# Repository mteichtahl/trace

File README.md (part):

# trace

trace runs a repository by itself and gives Claude the tools to do electronics work in it. It is generalised from
the loop that runs Potroller.

- **The loop.** A pushed branch gets its pull request, stacked on the open pull request it builds on when it builds on
  one (docs/stacked-changes.md). A PR merges itself when its required check passes, bottom of a stack first, and open
  PRs are brought up to date one at a time. A failing build is triaged: flaky failures are re-run, and real ones go to
  Claude, which fixes them. Deploys run behind a risk check, a smoke test and an automatic rollback. A person is asked
  only when a project's rules say so, or when the loop is stuck.
- **The tools.** These cover KiCad (reading schematics and boards, ERC/DRC, BOM, fabrication outputs), component
  calculators, SPICE and Verilog simulation, a datasheet library and parts database shared by every project,
  hardware-in-the-loop (serial, CAN, and SCPI power supplies, scopes and meters), and the firmware loop (build, flash,
  logs). They are reachable from the `tracectl` CLI and, for Claude Code, from the `trace` MCP server.

## Installing

```sh
npm install -g github:mteichtahl/trace#main    # the `tracectl` CLI (Node 22.13+; git, which this needs anyway)
tracectl install                               # opens the installer in your browser
```

The command is `tracectl`, not `trace`: macOS ships its own `/usr/bin/trace` (kernel tracing), and a `trace` on
`PATH` would shadow it, or be shadowed by it wherever nvm's directory is not first (sudo, cron, launchd). The
product, the MCP server (`claude mcp add trace -- tracectl mcp`) and `.trace/` keep the name.

**What you need:** AWS credentials (a profile, SSO included, or access keys; an administrator is simplest) and one
GitHub token. Nothing else: no Docker, no `gh` CLI, no KiCad or Python on this machine (the images build in
CodeBuild, and onboarding talks to GitHub's API and `git`).

The token: a fine-grained token (github.com/settings/personal-access-tokens) on the repositories trace will run, with
Contents, Pull requests, Issues, Workflows, Actions, Secrets, Variables, Administration and Webhooks read and write,
Deployments read, and the account permission "Email addresses: read"; or a classic token with `repo`, `workflow` and `user:email`. What each
permission is for, and what happens without it, is in [Tokens and permissions](#tokens-and-permissions).

Builds need nothing more. Every GitHub Actions job runs on an AWS CodeBuild runner in your account, trace's own
repository's included, and on GitHub's runners only until that runner exists. CodeBuild reaches GitHub through an AWS
CodeConnections connection already authorized in the account and region when there is one, else through that same
token (see [Where builds run](#where-builds-run)), so the first deploy has the runners and no console step is needed.

The installer is a page served from your own machine (127.0.0.1, with a one-time key in its address). It has four
steps, and only the first asks for anything:

1. **Connect.** The credentials and the token, then **Check**. Everything below is checked at once, before anything
   is created, and each finding says what to do (`src/installer/preflight.ts`); where the installer can fix it itself
   it offers a button, and does nothing until you press it.
2. **Projects.** The repositories the token sees, to tick, or **Create a new project** (a repository made and
   scaffolded from a KiCad, Rust, Python or empty template), or **Install the sample project** (see
   [The sample project](#the-sample-project)). None is fine: install now, add repositories by running the installer
   again.
3. **Integrations (optional).** Keys for Nexar, Mouser or Digi-Key, each checked with its service. Skippable; see
   [Optional integrations](#optional-integrations).
4. **Review.** The plan, how long it takes, and **Advanced**, which holds every other setting with its default.

**Worked out, not asked** (`src/installer/derive.ts`):

| Setting | From |
| --- | --- |
| Account | STS `GetCallerIdentity` (a second run stops if the credentials now resolve to another account) |
| Region | The profile's region, else `us-east-1` (Advanced to change) |
| GitHub login | The token (`GET /user`) |
| First administrator | The token's verified primary email (`GET /user/emails`); asked for under Advanced only when the token cannot see it |
| Model | The newest Claude Sonnet inference profile active in the region, the region's geography before `global.` |
| GPU and CPU jobs | On when the account's quotas allow one job (G and VT instances for GPU, standard instances for CPU), else off |
| Knowledge bases | On where the region has Amazon S3 Vectors |
| Prefix, session limits, bucket, observability, images | Their defaults (`trace`, 8 h, 15 min, a named bucket, on, prebuilt) |
| How the build runners reach GitHub | An authorized GitHub connection in the account and region, else the token ([Where builds run](#where-builds-run)) |
| Web app | On, at CloudFront's own address; a custom domain and email sign-in codes are optional ([Web app](#web-app)) |

**The preflight** checks, in parallel: the credentials; Bedrock AgentCore in the region; the model's inference
profile and the account's access to it (`GetFoundationModelAvailability`; for Anthropic, whether the one-time use-case
form was sent, `GetUseCaseForModelAccess`); Amazon S3 Vectors; the G and VT and standard-instance quotas (Service
Quotas) and the region's VPC quota; the CDK bootstrap (present, healthy, version 6 or later); the trace stack (none,
updatable, or stuck after a failed first deploy); names a removed installation kept (its image repositories and token
secret) that a new stack would collide with; the Cognito domain `<prefix>-<account>`; how the build runners will reach GitHub (an authorized GitHub connection, or
CodeBuild's GitHub credential, which with the token must be allowed to make each repository's webhook);
the token, its email, and whether trace's own actions can be used from other repositories; and, per chosen
repository, exactly which permission is missing and what that costs. What it offers to do:

| Finding | What the installer can do (on request) |
| --- | --- |
| Anthropic's first-time-use form not sent | Send it (`PutUseCaseForModelAccess`) with your answers; once per account or organisation |
| No access to the model yet | Accept its agreement (`ListFoundationModelAgreementOffers`, `CreateFoundationModelAgreement`; needs `aws-marketplace:Subscribe` and a payment method) |
| G and VT quota below one job (4 vCPUs) | Leave GPU and CPU jobs off and request 16 vCPUs (`RequestServiceQuotaIncrease`); turn them on and run again once granted |
| Standard-instance quota below one CPU job, or the region's VPCs full | Request an increase |
| The stack is `ROLLBACK_COMPLETE` (a failed first deploy) | Delete it, so the next install can create it |
| A removed installation's image repositories and token secret | Delete them |
| trace's actions not shared (a private source repository) | Share them with repositories of the same owner, when the token is its admin |

Model access never blocks installing: the stack deploys without it, and the agents work once it is granted.

It then runs the plan:

- **AWS (CDK):** one stack (bootstrapped first if needed). It contains the central bucket, the agent image and the
  tools image (both arm64, see [Images](#images-copied-or-built)), and AgentCore runtimes from the agent image: one
  worker runtime per project, each with its own execution role, GitHub OIDC role, GitHub token secret, memory,
  knowledge base, GPU and CPU job definitions, tools function (AWS Lambda, running the tools image: KiCad, Blender,
  the FPGA and verification tools, CalculiX, ffmpeg, build123d; see `agent/README.md`), cad function (the same image on
  a role with no S3, where the project's case script runs; see [Enclosures](#enclosures)) and CodeBuild build runner (see [Where builds run](#where-builds-run)), and the API runtime. Each project's
  resources are in a nested stack of their own (see [Stack layout](#stack-layout-and-limits)). A project's worker is
  invoked by that repository's workflows through IAM, and by the API. The API runtime is for people and is reached
  only with a Cognito sign-in. The stack also holds the Cognito user pool. Before the deploy, the token becomes
  CodeBuild's GitHub source credential when the runners use it; after it, only when the runners wait for a GitHub
  connection nobody has authorized yet, the installer waits for that and deploys again with them.
- **Integrations:** any keys given, stored as `<prefix>/integrations/<name>`.
- **GitHub, several repositories at once:** each repository's Actions variables (`TRACE_AWS_ROLE`,
  `TRACE_AGENT_RUNTIME_ARN`, `TRACE_MEMORY_ID`, `TRACE_KB_ID`, `TRACE_KB_DATA_SOURCE_ID` and `TRACE_CODEBUILD_PROJECT`,
  all its own project's, `TRACE_AWS_REGION`, `TRACE_HOME`, `TRACE_AGENT_LOGIN`) and its `TRACE_TOKEN` secret (its
  project's agent token, encrypted with the repository's key); and its onboarding pull request, or, when it is onboarded already and the trace workflows
  have changed, a held pull request refreshing them (`src/installer/onboard-api.ts`). trace's own repository gets
  `TRACE_CODEBUILD_PROJECT` alone, and `TRACE_UPDATE_ROLE`, `TRACE_AWS_REGION` and `TRACE_STACK` so the installation
  keeps itself up to date (see [Staying up to date](#staying-up-to-date)). `TRACE_CODEBUILD_PROJECT` is set only once
  the repository's build runner exists.
- **People:** Cognito invitations into each person's class group, at once, and project assignments recorded in the
  central database, one after another (it is one file).
- **Ready.** The page says trace is ready to use (`tracectl login`). Only then does it wait for **the GPU image**: the
  deploy starts it and does not wait for it (see [GPU jobs](#gpu-jobs-rendering-and-autorouting)), and it starts it
  again if an earlier one failed. A failed GPU image leaves GPU and CPU jobs unavailable and everything else
  installed.

**How long** (estimates from what each step does; not yet measured on a real account):

| | First install | Re-run or upgrade |
| --- | --- | --- |
| CDK bootstrap | about 2 minutes, when the region has none | none |
| The stack | about 15 minutes of CloudFormation, plus the agent image: about 5 minutes to copy a published one, 20–40 to build it | a few minutes for settings or projects; 5–10 when trace changed (the image rebuilds from its cache, or is copied) |
| Repositories, runners, onboarding, people | 1–2 minutes, in parallel | the same |
| GPU image (after trace is ready) | about 10 minutes to copy, 30–60 to build | from its cache |

Before this change the first install was the bootstrap, then 20–40 minutes for the agent image inside the deploy, then
each repository and person one after another, and only then the 30–60 minute GPU image before the page said anything
was done: about 60–110 minutes to a usable trace on a GPU-enabled account. Now it is about 20–25 minutes with a
published image (35–60 when it builds), and the GPU image no longer stands in the way.

**Running it again** updates the installation: the preflight says so, the plan lists what changes since the last run
from this machine (projects added or removed, settings changed, people), and CloudFormation leaves the rest alone.
Every step is safe to repeat. Adding or removing a repository adds or removes that project's runtime, roles, secret,
job definitions and runner.

Tokens and keys stay in the installer's memory. They are written only to Secrets Manager, to GitHub (encrypted), and,
when the build runners use the token, as CodeBuild's GitHub source credential (see [Where builds run](#where-builds-run)).

### The sample project

**Install the sample project**, on the Projects step, adds a new repository (`<your login>/trace-sample` unless you
name another): a small, finished sensor board from intent to fabrication files (`templates/sample`). It is the
quickest way to see the whole system work before you bring your own design, and it can be the only project.

- **It is a new project like any other:** the installer creates the repository with the other new ones, and it gets
  its own runtime, roles, memory, knowledge base and build runner; you can assign people to it. Onboarding fills it
  with the sample's files and settings, seeds its project database (requirements, a test plan using every method,
  analog and protocol specifications, thermal data) and pushes it all to `main`, with no pull request to merge.
  Its journey starts too, as a project made in the web app does: the Mixed template, at Define, so the web app shows
  its stages and gates from the start.
- **The tour,** last, opens one task per step of the journey (define, architect, capture, prove, layout, sign-off,
  release, bring-up), each labelled for the agent that takes it. Together they run every agent and every tool,
  every simulation included: circuit (ngspice), mixed-signal, logic, formal and coverage, FPGA synthesis and place
  and route, protocols, thermal (2.5D, CalculiX and CFD), electromagnetic (openEMS), autorouting (Freerouting and
  OrthoRoute), rendering (Blender), firmware, and hardware in the loop on an emulated bench (`tracectl hil emulate`).
  The tasks that need GPU or CPU jobs wait for the GPU image (and are left out when GPU jobs are off). The tour runs
  on AWS like any other work and costs what that work costs; untick **Start the tour** to install the sample without
  it. Running the installer again opens only the tasks that are missing.

`test/installer/sample-tour.test.ts` keeps the tour complete: a tool, agent or kind of remote job added without a
tour task fails it.

### Tokens and permissions

One token does everything. On each repository it needs:

| Permission (fine-grained) | For | Without it |
| --- | --- | --- |
| Contents, Pull requests, Issues, Workflows, Actions: read and write | The agents' work, the onboarding PR | Onboarding fails for that repository |
| Secrets, Variables: read and write | Its `TRACE_TOKEN` secret and variables | Refused for that repository, unless an admin token is given |
| Administration: read and write | Its settings and the "trace" ruleset; with the token as CodeBuild's credential, CodeBuild registering each job's runner | Settings and ruleset left alone; with the token as CodeBuild's credential the preflight stops: its runner can't be made |
| Webhooks, Commit statuses: read and write | With the token as CodeBuild's credential, its runner's workflow-job webhook; and the web app's live updates from GitHub | The same (a GitHub connection needs neither); live updates are a warning, and its screens look again every 60 s |
| Deployments: read | The project's last deploy in its status (the app and chat) | Its status says the last deploy is unreadable; the rest still shows |
| Email addresses: read (account) | The first administrator's email | The email is asked for |

A classic token needs `repo`, `workflow` and `user:email`, and its account must be an admin of each repository. The
preflight probes each permission without changing anything and names the missing ones per repository.

**The optional second token** (Advanced → Admin token): when the agents' token is deliberately narrow (no Secrets,
Variables or Administration, which the agents never need), give an admin token for the installation; it is used only
while installing and never stored, unless you choose it as the token CodeBuild keeps (Advanced → Build runners). A project's own agent token
(Advanced) isolates that project's agent on GitHub, as [Project isolation](#project-isolation) explains.

**trace's GitHub app** (its own rate limit). The workflows' harness steps (`open-pr`, `automerge`, `update-queue`,
`ci-doctor`) act as trace's GitHub app when it is installed on the repository: each job gets an installation token for
that repository alone, good for an hour, with the app's own quota (5,000 requests an hour and more, per installation).
Without it they spend the quota of the person whose token `TRACE_TOKEN` is, which ten open pull requests and busy agents
used up in an hour (test-esp32 run 2, #126). The app's private key is never a repository secret: it is kept in Secrets
Manager (`<prefix>/github-app`), and only the installation's token broker reads it (`<prefix>-github-app-token`, a
Lambda function URL with IAM sign-in, [docs/agent-identity.md](docs/agent-identity.md)). The broker picks the repository
from the AWS role that asks, never from the request. What each project repository needs for it:

| What | Where | For |
| --- | --- | --- |
| The broker's address | Variable `TRACE_GITHUB_APP_BROKER` | Where the steps ask for the app's token |
| The repository's token role | Variable `TRACE_GITHUB_APP_ROLE` | Assumed by GitHub OIDC from any of the repository's workflow runs (branches and pull requests too: `open-pr` and `automerge` run there, and the default-branch role `TRACE_AWS_ROLE` cannot be assumed there); it may do nothing but ask the broker |
| The app installed on the repository | The app's installation | Its token; not installed: `TRACE_TOKEN`, with a notice |
| Contents, Pull requests, Issues, Actions: read and write; Checks, Metadata: read | The app's permissions | What the steps do; a request the app is refused is made with `TRACE_TOKEN` instead, with a warning naming it |

Still `TRACE_TOKEN`'s: opening a pull request (trace tells its changes apart by the login that opened them,
`TRACE_AGENT_LOGIN`), pushes made with git (not API requests, so no quota), and a step without the broker (no variables,
a role that could not be assumed, a broker that refuses or does not answer: the step's log says which). The app needs no
`workflows` permission: a branch update that changes `.github/workflows/**` falls back to `TRACE_TOKEN`. The agents'
own steps (Claude's pushes and comments) keep `TRACE_TOKEN` for now (`src/harness/app-token.ts`).

**Nothing on the default path needs the AWS console.** The preflight's fixes are API calls (the Anthropic use-case form,
`PutUseCaseForModelAccess`; the model agreement, `CreateFoundationModelAgreement`; quota increases,
`RequestServiceQuotaIncrease`; a failed first deploy, `DeleteStack`; a stuck rollback, `ContinueUpdateRollback`; a
removed installation's sign-in domain, `DeleteUserPoolDomain`; its kept repositories and secret), the build runners
use the token unless a connection is authorized already, and publishing images is set up by API too. What a person
still decides, and why:

| What | Why it can't be automated | When it comes up |
| --- | --- | --- |
| Authorizing a new AWS CodeConnections connection | AWS requires the GitHub app's installation to be approved in the console (the OAuth handshake with GitHub) | Only with Advanced → Build runners → "An AWS CodeConnections connection" and none authorized yet |
| Waiting for AWS: a pending Anthropic agreement, a quota increase | AWS decides (it emails; usually minutes for the agreement, within a day for a quota) | Only when the preflight found them missing; installing never waits |
| A payment method on the account | The model agreement is an AWS Marketplace subscription, which needs one (Billing) | Only on an account that has none |
| A custom ECR Public alias | Requested in the console only | Never: trace uses the registry's default alias |
| Sharing a private trace source repository's actions | GitHub requires that repository's admin | Only when you are not its admin |

### Optional integrations

Keys for external services some tools use. None is needed to install or deploy; without one, the tools that use it
carry on with what they have and say which key would add more ("no Nexar (Octopart) credentials …: add them with
`tracectl integrations set nexar`").

| Integration | Keys | Enables | Get one |
| --- | --- | --- | --- |
| `nexar` | `NEXAR_CLIENT_ID`, `NEXAR_CLIENT_SECRET` | Stock, prices and lifecycle from every distributor Octopart lists (parts lookup, search, alternatives, BOM checks) | [portal.nexar.com](https://portal.nexar.com/) |
| `mouser` | `MOUSER_API_KEY` | Mouser stock, prices, lifecycle, datasheet links | [mouser.com/api-hub](https://www.mouser.com/api-hub/) |
| `digikey` | `DIGIKEY_CLIENT_ID`, `DIGIKEY_CLIENT_SECRET` | Digi-Key stock, prices, lifecycle, datasheet links | [developer.digikey.com](https://developer.digikey.com/) |
| `dhl` | `DHL_API_KEY` | Following a shipped order's DHL parcel ([Cost and orders](#cost-and-orders)); read by the order watch only, kept as `<prefix>/order-watch/dhl`, never by a worker | [developer.dhl.com](https://developer.dhl.com/api-reference/shipment-tracking) |

LCSC needs no key, and the datasheet tools fetch public URLs; those are every credential the tools read
(`src/core/integrations-catalog.ts`, checked by `test/core/integrations.test.ts`).

```sh
tracectl integrations list                      # which are set, what each enables
tracectl integrations set nexar                 # asks for the keys (or NEXAR_CLIENT_ID=… NEXAR_CLIENT_SECRET=…)
tracectl integrations check nexar               # the stored keys, checked with Nexar
tracectl integrations remove nexar
tracectl integrations set mouser --remote       # through the API, as a signed-in admin
```

Each is one Secrets Manager secret, `<prefix>/integrations/<name>`, written by the installer, the CLI (your AWS
credentials) or an admin through the API (`integrations.set`, `.list`, `.remove`; the API may write them and never
reads them back). A key is checked with its service when given; a failed check is reported and the key stored anyway.
With the library gateway off, each worker role may read `<prefix>/integrations/*`, and the worker loads them into its
environment when it starts (so an agent, which has Bash and its role's credentials, can read them too). With the
[library gateway](#library-gateway) on, only the gateway's Lambda may read them and no worker role can. A changed key
reaches workers at their next session and the Lambda at its next cold start; nothing is redeployed.

### Images: copied or built

The three images (the agent's, arm64, at most 2 GB for AgentCore; the tools functions', arm64, with the programs too
large for it; the GPU and CPU jobs', amd64) are made by CodeBuild in your account (`src/infra/images.ts`):

- **Prebuilt** (the default): CodeBuild copies trace's published image for exactly this source from Amazon ECR Public,
  `<registry>/trace-agent:<content tag>`, `/trace-tools:` and `/trace-gpu:`, into the installation's own private
  repository. The
  content tag is a hash of what goes into the image, computed the same way by the stack and by trace's release
  workflow (`scripts/image-tag.mjs`), so a modified trace never takes an image that is not its own. The copy is pinned:
  `scripts/resolve-image.mjs` reads the tag's digest from the registry and checks it against the manifest's own
  bytes, the image is pulled by that digest, its digest is checked again after the pull, and only then is it re-tagged
  and pushed. When the tag is not published (an unreleased commit, a fork), or no registry is set, it builds instead.
  `<registry>` is found at install time: the source repository's `trace-images` release, which publishing writes
  (below), names it. Nothing published yet, so always built until then. Advanced → "Published images registry"
  overrides it, and `PUBLISHED_REGISTRY` in `src/infra/props.ts` can pin one for a fork; neither is needed.

  AgentCore would also run an image straight from `public.ecr.aws` (its `containerUri` accepts it), and Batch could
  pull one; trace copies it anyway, so the runtimes and jobs pull from the account's own registry in their region (no
  public pull rate limits, no dependence on ECR Public at each cold start, the image stays if a release is withdrawn),
  and the private repository keeps its lifecycle rule (the last 10 images).
- **Build:** `docker build` with BuildKit's inline cache: the previous image (`:cache`) is the cache, so a rebuild
  after an upgrade redoes only the layers whose inputs changed, and CodeBuild's local Docker layer cache helps a build
  soon after another.

An installed trace has no `package-lock.json` or `.npmrc` (npm never packs them), and both the images and the CDK's
Lambda bundling need the lock file: `npm run build` copies both into `agent/`, which npm packs
(`scripts/stage-image.mjs`, `src/infra/lockfile.ts`).

### Publishing images

trace's own images are published to Amazon ECR Public from one AWS account, the project owner's, so every
installation can copy them. Publishing is a step of the install itself, with no prework: when the GitHub token you
install with administers trace's source repository, the installer sets publishing up from that account and starts
the first release (the preflight says so, and Advanced → "Publish trace's images" turns it on or off). Nothing is
done in the console, and nothing is edited or committed. `tracectl release setup --publish` does the same on its own.

It (`src/installer/release.ts`):

1. bootstraps CDK in us-east-1 (ECR Public's only region) when it isn't, and deploys **TraceRelease**
   (`src/infra/release.ts`; `npm run deploy:release` deploys it alone): the public repositories `trace-agent`
   and `trace-tools` (linux/arm64) and `trace-gpu` (linux/amd64) with their gallery catalog data, and the release role `trace-release`,
   which GitHub OIDC lets only the source repository's `main` and `v*` tags assume, and which may only log in and push
   to those three repositories (the account's GitHub OIDC provider is used when it has one);
2. reads the registry's address, `public.ecr.aws/<alias>`, with `DescribeRegistries`. The alias is the registry's
   default one, which ECR Public assigns by itself once the account's first public repository exists, so a new
   registry gets it right after the deploy (setup waits a minute for it). A custom alias is the only kind that needs
   the console, and trace does not use one. The gallery display name is set with `PutRegistryCatalogData`;
3. sets the source repository's variables `TRACE_RELEASE_ROLE` and `TRACE_IMAGE_REGISTRY` with the GitHub token you
   gave (REST);
4. records the registry in the source repository's `trace-images` release (a pre-release, never "latest"), where every
   installer finds it;
5. starts the first release (`workflow_dispatch`; the CLI with `--publish`) and prints where the images appear
   (`public.ecr.aws/<alias>/trace-agent`, `https://gallery.ecr.aws/<alias>/trace-agent`, and the same for `trace-tools` and `trace-gpu`).

From then on every merge to `main` and every `v*` tag publishes (`.github/workflows/release-images.yml`, which does
nothing until both variables are set). It runs on the source repository's own AWS build runner, which the
installation makes (with Docker, when it publishes; see [Where builds run](#where-builds-run)), and on GitHub's
`ubuntu-24.04` runner until that exists. It builds both images with BuildKit, caches in the registry
itself (`:cache`, mode=max), attaches an OCI provenance attestation, tags the content tag plus `latest` on main and
`vX.Y.Z` on a tag, and records each pushed digest in the job summary. Installations look there from then on by
themselves: each install reads the `trace-images` release, and copies its version's images when they are published.

### Upgrading and uninstalling

```sh
tracectl upgrade              # pull the newer trace (npm install -g github:mteichtahl/trace#main), then redeploy with the
                           # saved answers and refresh each repository's variables and workflows
tracectl upgrade --check      # what it would change, without changing anything
tracectl upgrade --runner-auth token|connection|auto   # switch how the build runners reach GitHub (Where builds run)
tracectl upgrade --connection ARN|auto   # choose the GitHub connection the build runners use (auto: the installer's pick)
tracectl uninstall            # remove it (asks you to type the stack's name; --yes to skip)
```

Running trace from a clone (`npm link`)? `tracectl upgrade` doesn't pull it from GitHub: update the clone (`git pull && npm ci && npm run build`), then run `tracectl upgrade --no-pull`.

Both use the answers saved on this machine and your AWS credentials; the GitHub token is read back from the
installation's own secret, so neither asks for it. `tracectl uninstall` removes the integrations' secrets, each
repository's trace variables (`TRACE_CODEBUILD_PROJECT` among them) and `TRACE_TOKEN`, trace's own repository's
`TRACE_UPDATE_ROLE`, `TRACE_STACK` and `TRACE_AWS_REGION` (see [Staying up to date](#staying-up-to-date)), the stack (and with it the
build runners and their webhooks), then CodeBuild's GitHub credential when trace imported it, and lists what stays (a
GitHub connection the stack created among it): with keep data (`retainData`, the default) the central
bucket, the image repositories, each project's memory, log groups and knowledge-base vectors; always the Cognito user
pool, the API's token secret, the CDK bootstrap, Transaction Search and the files onboarding added to each repository.
`--delete-data` also deletes what would block installing again with the same prefix (the image repositories, the token
secret, the user pool) and prints the commands for the bucket and the memories.

## Project isolation

Each project's agent runs Claude with Bash, so it can use its runtime's AWS credentials directly. The line between
projects is therefore drawn in IAM, not only in code (`src/infra/project.ts`):

| Isolated per project | How |
| --- | --- |
| **Worker runtime** | One AgentCore runtime per repository (`<prefix>_w_<hash>`, tagged `trace:project`), with its own execution role and `TRACE_PROJECT=owner/repo`. It refuses, with a 403 that is logged, any invocation or job for another repository. |
| **Memory** | One AgentCore Memory per repository (`<prefix>_m_<hash>`, tagged `trace:project`), its own event expiry, and its own log group and log delivery. The worker is told only its own (`TRACE_MEMORY_ID`) and its role may use only that memory's ARN. On it, the role may still create and list events only for actors `<owner>/<repo>/*`, and recall and list records only under `/trace/<owner>/<repo>/*` (the condition keys `bedrock-agentcore:actorId` and `bedrock-agentcore:namespace`), as defence in depth. The actor comes from `TRACE_PROJECT`, never from the request. The GitHub OIDC role has the same grants on the same memory, for the `worker.runner = actions` fallback (the repository variable `TRACE_MEMORY_ID`). |
| **S3** | Read and write `projects/<owner>/<repo>/*` and `jobs/<owner>/<repo>/*`, and list only those prefixes and `central/*`. Read, never write, `prompts/*` (the installation's prompt overrides, see [Managing prompts](#managing-prompts)). Nothing under `access/*`, and nothing of another project. |
| **GPU and CPU jobs** | Two AWS Batch job definitions per project (`<prefix>-gpu-<hash>`, and `<prefix>-cpu-<hash>` with the CPU queue), with one job role that reads and writes only that project's `jobs/<owner>/<repo>/*`. A project's role may submit only with its own definitions, only jobs tagged `trace:project=<owner>/<repo>`, and may stop only jobs carrying that tag. SubmitJob cannot override a definition's job role. |
| **Tools and cad functions** | Nested layout: two AWS Lambda functions per project from the tools image. The tools function (`<prefix>-tools-<hash>`) runs trace's own programs (KiCad, Blender, the FPGA tools, CalculiX, ffmpeg, the enclosure engine's checks) on a role that reads and writes only `jobs/<owner>/<repo>/*` and its own log group. The cad function (`<prefix>-cad-<hash>`) runs the project's case script (`mechanical/case.py`, code a person or a pull request wrote) on a role that may write its own log group and nothing else: no S3, no X-Ray. The worker signs 20-minute URLs for that one job's files and sends only those (`src/gpu/urls.ts`), so a script that reads the runner's credentials or `/proc` finds nothing that reaches another object, and whatever it writes back is a claim the tools function measures. Only the project's worker may invoke either. The flat layout has its tools functions in one nested stack and no cad functions: a custom case script builds there on a laptop or in CI. |
| **Events** | Nested layout only. One SNS topic per project, `<prefix>-<hash>-batch-events`, and up to two EventBridge rules sending it events: its own Batch jobs' state changes (with GPU jobs), and `<prefix>-<hash>-journey-events`, the central bucket's "Object Created" event for its journey record (`projects/<owner>/<repo>/journey/journey.db`, which only the API writes), its job index (`journey-agent/jobs.db`) and its agents' facts (`journey-agent/facts.db`, where a hand-off's answer is written). Only those rules may publish to it. A worker waiting on a job, on a person's answer in `journey.ask`, or on a hand-off's answer in `journey.handoff`, subscribes a short-lived queue of its own (`<prefix>-<hash>-wait-*`) and is told at once. It still checks on a slow timer (30 seconds and 90 seconds after subscribing, then every 5 minutes) in case a message is lost. Without the topic (flat layout, or an older stack) it checks on a timer and says when it will look next. |
| **Knowledge base** | One Amazon Bedrock knowledge base per repository (`<prefix>-kb-<hash>`, nested layout only), with its own service role (`<prefix>-kb-<hash>-<region>`) that reads only `projects/<owner>/<repo>/kb/*` and its own S3 Vectors index, and invokes only the embedding model. The worker role and the OIDC role may `bedrock:Retrieve` and start, get and list ingestion jobs on that knowledge base's ARN only. See [Knowledge base](#knowledge-base). |
| **Library gateway** | Off by default (`gateway.enabled`). When on, each worker role may `bedrock-agentcore:InvokeGateway` on the installation's one library gateway and nothing else of it; the gateway serves only the shared datasheets and parts tools. See [Library gateway](#library-gateway). |
| **GitHub OIDC role** | One per repository, trusted only for `repo:OWNER/REPO:ref:refs/heads/BRANCH`, and for the same branch under GitHub's immutable subject `repo:OWNER@OWNER_ID/REPO@REPO_ID:…` (what GitHub sends for repositories created, renamed or transferred after 15 July 2026, or opted in; the installer reads the ids from GitHub). It may invoke only that project's runtime, read and write only that project's prefix (and the central database), and use only that project's memory and knowledge base, as its worker does. |
| **GitHub token** | Each project has its own secret, `<prefix>/github-token/<owner>/<repo>`, and its worker reads only that one. This isolates GitHub access only when you give the project its own fine-grained token limited to that repository. By default the shared token is copied into every project's secret, and the installer's summary says so. A project token is checked: it must see its repository, and the installer warns if it can also see another project's. |

Shared on purpose:

- **The central database** (`central/`: datasheets and the parts database). Every project reads it. Every project
  may also write it, because adding a datasheet is a shared write, but only with a conditional put (`If-Match` or
  `If-None-Match`, which is how the central store always writes) and never a delete. The bucket is versioned.
- **The library gateway** (when `gateway.enabled`): one AgentCore Gateway and its Lambda, which reach the central
  store and the distributor keys only. See [Library gateway](#library-gateway).
- **The GPU and CPU queues and compute environments**, and the GPU image (which both run).
- **The S3 vector bucket** that holds every project's knowledge base index (one index per project; each service role
  reaches only its own index's ARN).
- **The agent image**: every runtime runs the same one. **The tools image**: every project's tools function runs it.
- **The API runtime.** It is the one component that spans projects. It holds the shared GitHub token, which admins
  need for `settings.get` and `settings.set` on any project. It reads (never writes) the records of every project's
  memory for `memory.list` and `memory.recall`, choosing the memory of the project asked for after the access check,
  it may `bedrock:Retrieve` on every project's knowledge base for `kb.search`, again after the access check,
  and it may invoke every project's worker: each by its exact runtime ARN, and the runtime only when it carries this
  installation's tag `trace:installation=<prefix>` (`aws:ResourceTag`, which the Service Authorization Reference
  lists for both of InvokeAgentRuntime's resource types, runtime and runtime-endpoint; the endpoint statement names
  the exact ARNs only, because the `DEFAULT` endpoint AgentCore makes is not tagged by the stack). No name pattern, so
  another installation in the account is out of reach. It does all of this only after its
  Cognito access check. It runs no model and no agent, and nothing reaches a shell through it: a `task` is handed to
  the project's own worker runtime.

`DescribeJobs` in AWS Batch has no resource-level permissions, so any project's role can describe (not change) any
job on the queue, which includes its command and environment. Job ids, not data, are what that reveals.

### Stack layout and limits

An installation holds up to 60 projects. Each project's resources (its worker runtime and execution role, GitHub
OIDC role, token secret, memory with its log group and log delivery, GPU and CPU job definitions and job role, and its
knowledge base with its index, service role and data source: 23 CloudFormation resources with everything on) are a CloudFormation nested stack of their own, `Project<hash>Stack`
(`src/infra/project.ts` `ProjectNestedStack`). The parent stack holds the shared parts and one
`AWS::CloudFormation::Stack` per project. What a project uses of the parent (the bucket, the agent image and its
repository, the OIDC provider, the GPU and CPU queues, image repository, execution role and log group) reaches its
nested stack as parameters (the S3 vector bucket too), and the parent waits for Transaction Search before it creates or updates a project (not
for the GPU image: see [GPU jobs](#gpu-jobs-rendering-and-autorouting)).
Inside, the resources are the ones the single stack had, with the same names, IAM and removal policies (with
`retainData`, a removed project's memory, log group and log delivery stay in the account, as before).

| Projects | Parent stack: resources / outputs | Each project's nested stack: resources / outputs / parameters |
| --- | --- | --- |
| 1 | 89 / 20 | 23 / 15 / 12 |
| 24 | 115 / 20 | 23 / 15 / 12 |
| 60 | 152 / 20 | 23 / 15 / 12 |

(Everything on, including the legacy memory's one-deploy output and the CI runners' role. The knowledge bases add the vector bucket to the
parent, and to each nested stack five resources, its two outputs `Project<hash>KnowledgeBaseId` and
`Project<hash>KnowledgeBaseDataSourceId`, the knowledge base id the parent reads for the API, and the vector bucket's
parameter. From 24 projects, CDK moves part of the API role's policy, which names every project's memory, worker
runtime and knowledge base, into managed policies of that role: three at 24 and four at 60, of the ten a role may have
by default. The tools functions add five resources and the `ToolsImageUri` output to the parent, for the tools image
(its repository, its CodeBuild project with its role and policy, and its build), and to each nested stack four
resources (the function, its role, policy and log group: `src/infra/tools.ts`) and three parameters (the tools
image's repository and tag); the cad function (`CadFunction`, the case script's) adds the same four to each nested
stack, 39 with everything on. The flat layout has no room for those per project, so its tools functions are all
in one nested stack, one resource of the parent's, left out when the parent has no room even for that, and it has no
cad functions: see `agent/README.md`.)

CloudFormation allows 500 resources, 200 outputs and 200 parameters per template, and the stack checks all three
when it is built. The parent carries none of a project's outputs, so its output count does not grow with the
projects. Each project's are its nested stack's, under the names they always had (`Project<hash>RuntimeArn`,
`Project<hash>ActionsRoleArn`, `Project<hash>MemoryId`, `Project<hash>GithubSecretArn`,
`Project<hash>GpuJobDefinition`, `Project<hash>LogGroup`, `Project<hash>MemoryLogGroup`), with `Repository`
(`owner/repo`). The installer lists the parent's resources (`ListStackResources`: `DescribeStackResources` returns
only the first 100), takes each `AWS::CloudFormation::Stack` whose logical id is `Project<hash>Stack…`, reads its
outputs with `DescribeStacks` on its physical id, checks its `Repository` output against the hash, and takes only the
outputs named for that hash (`src/installer/aws.ts` `stackOutputs`). The flat layout keeps its outputs in the one
stack, as before. The other limit at 60 is the API's three `owner/repo=<id>` lists (see
[Agent memory](#agent-memory)): very long repository names can reach their 5000 characters first, and the stack says
so when it is built. The output `Layout` says which layout an installation has.

`cdk deploy` uploads each nested template to the CDK bootstrap bucket as a file asset, the same way it already
uploads the agent source and the Lambda code, so the bootstrap the installer runs (version 6 or later) covers it.

**Installations from before nested stacks keep `layout: 'flat'`.** There every project's resources are in the one
stack, and it holds about 20 projects (`cdk synth` refuses more). A flat installation has no knowledge bases and no CPU
queue: at about 480 of its 500 resources with 20 projects, it has no room for them. The installer picks the layout from the deployed
stack: a stack with a `Layout` output keeps that layout, a stack without one is flat, and a new installation is
nested. Deploying by hand, set `layout: 'flat'` in `TRACE_INFRA` for an older stack.

Moving a flat installation to nested stacks is a choice in the installer ("Move to one nested stack per project"),
because it deletes every project's memory records. CloudFormation cannot move these resources in place:

| Resource | What a plain switch to nested would do |
| --- | --- |
| AgentCore runtime (`<prefix>_w_<hash>`), memory (`<prefix>_m_<hash>`), IAM roles (`<prefix>-w-`, `-gh-`, `-gpu-<hash>-<region>`), secret (`<prefix>/github-token/<owner>/<repo>`), delivery sources and destinations (`<prefix>-m-<hash>-…`) | CloudFormation creates a moved resource before it deletes the old one, and these names are fixed, so the nested stack's create fails on the first name already in use and the update rolls back. Nothing is lost, and nothing moves. A memory with `retainData` is also Retain, so even after its old copy is removed its name stays taken. A deleted secret can keep its name through its recovery window. |
| Batch job definition (`<prefix>-gpu-<hash>`) | Would work: registering an existing name adds a revision, and deleting the old resource deregisters only its own revision. |
| A memory's log group (`/aws/vendedlogs/…/<memory id>`) | Named after the memory's id, so a new memory gets a new log group. The old one stays with `retainData`. |

CloudFormation stack refactoring (2025, and `cdk refactor`) moves resources between stacks, nested ones included,
but only as an operation that creates, deletes and modifies nothing. This move has to create the nested stack
resources and their parameters, and to change the API runtime's environment, the API role's policy and the outputs
to read from the nested stacks. That would take a separate deploy for each of those changes around a refactor, and
refactoring also requires every moved resource type to be fully mutable, which has not been confirmed for the AgentCore
resource types. It was not chosen. Renaming everything once (a version suffix) would keep the records but change every
name for good, and the names are how projects are told apart in IAM.

The move is therefore three deploys in a row, run by the installer:

1. **release** (only with `retainData`; `layoutMigration: 'release'`): the same stack, with each project's memory and
   its log delivery marked Delete. Nothing else changes.
2. **drain** (`layoutMigration: 'drain'`): every project out of the stack. CloudFormation deletes each project's
   runtime, roles, secret, job definition, memory with every record in it, and log delivery. With `retainData`, each
   memory's log group stays in the account. The API is told no workers, so the projects are offline from here.
3. **nested** (`layout: 'nested'`): every project again, each in its own nested stack, with an empty memory. Just
   before it the installer force-deletes any project secret still in its recovery window (they are copies of tokens,
   and it writes them again straight after). Then it rewrites every repository's variables as usual.

Workflows that run between the second deploy and the variable update fail; re-run them. If a deploy fails, run the
installer again: it carries on from the layout the stack is then in.

**What a flat installation gets, and why the move is the way on.** Projects created in the web app are added to a flat
installation by the self-update too, while it holds fewer than 15 projects (`FLAT_UPDATE_MAX`, src/installer/pending.ts;
each project is about 21 of the stack's 500 resources, and an unattended deploy keeps room for trace's own changes);
past that, by the next installer run. They get their agent, memory and build runner, but no knowledge base, CPU queue or
per-project events topic, so an agent waiting in `journey.ask` checks the record on its timer. Giving the flat layout
those was rejected: the knowledge base (5 resources), the CPU job definition (1) and the events topic with its policy
and rule (3) would take 20 projects past 500 resources, so the flat cap would drop to about 15 for every existing
installation. The self-update never moves the layout, because the move deletes every project's memory records, which
is a person's call; the installer offers it ("Move to one nested stack per project"), and the app says all of this on
New project and Admin › Installation (`installation.layout`), with the move's steps and what it costs.

**Upgrading an installation from before per-project roles.** The next installer run replaces the single worker
runtime (`<prefix>_agent`), its role, the one GitHub OIDC role (`<prefix>-github-actions-<region>`) and the one GPU
job definition with one of each per project, and rewrites every repository's `TRACE_AWS_ROLE` and
`TRACE_AGENT_RUNTIME_ARN`. Workflows that run between the deploy and the variable update fail to assume the old
role; re-run them. The shared `<prefix>/github-token` secret stays, as the API's. GPU job files written under the
old `jobs/<id>/` layout expire with the bucket's one-week rule.

**Upgrading an installation from before per-project memory.** The installation-wide memory (`<prefix>_memory`) is
removed and every project starts with its own, empty memory. See [Agent memory](#agent-memory) for what happens to
the old one's records.

## People and permissions

Everyone signs in with Amazon Cognito (`tracectl login`). Each person is in one of three classes:

| Class | What they can do |
| --- | --- |
| **admin** | Everything, on every project. This includes inviting people, setting classes and assigning projects. |
| **user** | Read and write, only on the projects they are assigned to. |
| **guest** | Read only, only on the projects they are assigned to. |

- **Read** means seeing a project's status, settings, runs and artifacts, and using the read-only tools.
- **Write** also allows changing settings, giving the agents work (`tracectl remote task`), and using the tools that
  record runs.

A person's class is their Cognito group (`trace-admins`, `trace-users`, `trace-guests`), so it travels inside their
signed token. Someone in none of these groups can do nothing. Project assignments live in the central database.
Someone not assigned to a project cannot tell that it exists.

The API runtime checks every request against these rules. Each repository's own workflows reach only that project's
worker runtime, through IAM, so a person's sign-in never acts as the loop, and the loop never acts as a person. Admins manage
people with:

```sh
tracectl users invite EMAIL --class user|guest|admin
tracectl users class EMAIL guest
tracectl users assign EMAIL OWNER/REPO
tracectl users unassign EMAIL OWNER/REPO
tracectl users list
tracectl users assignments
```

The installer sets up the first admin and anyone else you list, with their classes and projects.

Changing a project's prompts takes write access on it, and the installation's prompts only an admin can change;
guests can list, read and preview them (see [Managing prompts](#managing-prompts)).

Marking an agent memory inactive (`tracectl remote memory deactivate`) takes write access. A person's own preferences
are the exception: they may mark those with read access alone (see [Inactive memories](#inactive-memories)).

## Connecting other systems

A **connected system** is another system or AI agent that calls trace with its own keys: a build dashboard, a release
pipeline, a script, an MCP client. Each one has a name, what it may do (read, or read and change) and the projects it
is on, as a reviewer or a contributor, exactly like a person. A project it is not on does not exist for it. The design
is in [docs/external-access.md](docs/external-access.md).

**Turning it on.** External access is off until an admin turns it on: run `tracectl install`, open **External
access**, switch it on and deploy. That adds a sign-in for systems and two addresses, one for scripts (the external
API) and one for AI agents (the MCP endpoint). Both cost nothing while nobody calls them. With it off, the admin screen
and `tracectl services` say so, and nothing outside can get in.

**Connecting one.** In the web app, **Admin → Connected systems → Connect a system**: a name, what it is for, what it
may do (Read only is recommended: it can look but not change anything) and its projects. A read-only system is always
a reviewer. Or from the command line:

```sh
tracectl services create build-dashboard --scope read --project acme/soil-sensor --description "The lab's wall screen"
tracectl services create release-bot --scope write --project acme/soil-sensor:contributor
tracectl services list
tracectl services show build-dashboard
```

Both show the client id and the **secret once**, with the sign-in (token) address, the API address and the MCP
address. trace does not keep the secret: store it at once, in a password manager or the other system's secret store.

**Getting a token.** The system swaps its client id and secret for a sign-in token that lasts an hour:

```sh
curl -s -u "$CLIENT_ID:$TRACE_CLIENT_SECRET" -d grant_type=client_credentials \
  --data-urlencode "scope=trace-external/read" "$TOKEN_URL"          # trace-external/read trace-external/write to change things
```

**Calling the API.** The same `{ action, ...args }` JSON as the app, with the token:

```sh
curl -s -X POST "$API_URL" -H "Authorization: Bearer $TOKEN" -H 'content-type: application/json' -d '{"action":"projects"}'
```

**Connecting an AI agent.** Point an MCP client (Claude Code, for example) at the MCP address. It gets one tool per
action the system may use:

```json
{ "type": "http", "url": "<MCP address>", "headers": { "Authorization": "Bearer <token>" } }
```

**What a system can and can't do.** With read it can see the projects it is on: their status, settings, runs and
artifacts, jobs, requirements, design, build and cost records, files, the knowledge base, and the read-only tools.
It can also read trace's records the way trace names them: the ontology's terms (`ontology.describe`), any record
as JSON-LD (`record.get`), what a run was made from (`artifact.lineage`) and which runs no longer stand
(`artifact.stale`).
With read and change it can also, where it is a contributor, give the agents work, pause or cancel its own jobs,
propose a settings change (as a pull request a person merges), sync the knowledge base and run tools that record
runs. Never, whatever it may do: anything that needs an admin, signing gates, answering questions, waivers, design
decisions, orders, chats, preferences, memory, prompts, people and assignments, or the tools of the shared datasheet
library and the parts search (shared by every project, and the parts search spends the installation's paid quota).
Those stay with a person. Anything else answers "no access", the same words as a project that isn't yours.

**Limits.** Each system may make 10 requests a second and 300 a minute, counted across the whole installation; over
that it is answered 429 with `Retry-After`, the number of seconds to wait. It may have at most three tasks queued or
running on one project; a fourth is refused until one finishes. An unexpected failure is answered
`internal error (ref …)`: the reference finds the details in the external runtime's log (`ExternalLogGroup`).

**Stopping and rotating.** Disabling a system stops it within 30 seconds; deleting it disables it first, then removes
its keys and takes it off every project. A new secret works beside the old one, so the system can switch without
stopping; retire the old one once it has:

```sh
tracectl services disable release-bot          # enable to let it in again
tracectl services rotate build-dashboard       # prints the new secret, once
tracectl services retire-secret build-dashboard OLD_SECRET_ID
tracectl services delete release-bot           # asks you to type the name; --yes skips that
tracectl services history build-dashboard
```

Every command takes `--json`. The web app has the same on each system's page.

**A leaked secret.** Disable the system first, then rotate, retire the old secret, give the new one to the system, and
enable it again. Rotating alone is not enough: the old secret keeps working until it is retired, and a token already
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
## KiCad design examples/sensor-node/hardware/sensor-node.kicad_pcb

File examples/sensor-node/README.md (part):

# sensor-node: one small design through the whole trace toolkit

A sensor input channel that takes 0–12 V and feeds a 3.3 V microcontroller's ADC. It's a real, finished design: the
schematic passes ERC, the routed board passes DRC with schematic parity, every part has a manufacturer part number
and an LCSC code, and every value comes from a trace calculator. The same circuit is also simulated, and the MCU side
has a Verilog filter with a testbench and a C conversion module with a unit test.

Every output shown below is from an actual run (KiCad 10.0.7, ngspice, Icarus Verilog, host `cc`). Run ids differ on
each run.

```
J1 VIN ──R1 39k──┬── DIV ──R3 6k2──┬──────────── ADC_IN ──► J2.3
                 R2 13k            C1 10n   D1 BAT54S clamp: ADC_IN to GND and to 3V3
                 │                 │        C2 100n on 3V3
                GND               GND
J2.4 LED ──R4 680── D2 red LED ── GND           J2: 1 3V3, 2 GND, 3 ADC_IN, 4 LED
```

| Folder | What it holds |
|---|---|
| `hardware/` | The KiCad 10 project: schematic, 2-layer 40×25 mm board, and project library tables pointing at KiCad's standard libraries. |
| `sim/` | `front-end.cir`, the analog path as an ngspice netlist with the schematic's values. `front-end-from-kicad.sh` simulates the schematic itself. `models/BAT54S.lib` is the vendor model for the clamp diode. |
| `logic/` | A 4-sample moving average for the ADC samples, and its self-checking testbench. The same checks are also written as cocotb tests (`test_moving_average.py`, run with `verify.cocotb`), and as formal properties (`moving_average_props.sv`, plus `moving_average.sby` for `verify.formal`). `spi_adc_slave.v` is the digital side of an SPI ADC reading ADC_IN, and `spi_adc_slave_tb.v` is its testbench, generated by `protocol.testbench` (section 7). |
| `firmware/` | `adc.c`, which converts ADC counts to input millivolts, plus a host unit test and a Makefile (`make`, `make test`). |
| `tools/` | `generate.ts` writes the KiCad files. `setup-db.ts` writes `.trace/project.db`. |
| `.trace/` | `project.db` holds the settings below and records every tool run. `rules.md` is left for the owner to write. |

Settings (`tracectl config show`):

- `electronics.projects` is `["hardware/sensor-node.kicad_pro"]`.
- `electronics.models` is `["sim/models"]`, so the BAT54S model is in every simulation.
- `firmware.targets` has one target: `adc-convert`, `make` preset, `path: firmware`, `build: make all test`, `artifact: build/libadc.a`.

Run everything below from this folder.

## 1. Choose the values

```
$ tracectl tool calc.divider vin=12 vout=3.0 series=E24
summary: "R1 39 kΩ / R2 13 kΩ (E24) gives 3 V (+0.00 %), worst case 2.96 V to 3.05 V"

$ tracectl tool calc.divider vin=12 r1=39k r2=13k
r_thevenin_ohm: 9750
summary: "Vout 3 V (worst case 2.96 V to 3.05 V at 1 %), divider current 231 µA"
```

The anti-alias filter's resistance is R3 plus the divider's Thevenin resistance (9.75 kΩ), because the divider is
what drives the filter.

```
$ tracectl tool calc.rc_filter fc=1k c=10n
summary: "R 16 kΩ, C 10 nF gives fc 995 Hz (-0.53 %)"
```

16 kΩ − 9.75 kΩ = 6.25 kΩ, and the nearest E24 value is 6.2 kΩ:

```
$ tracectl tool calc.rc_filter r=15950 c=10n
fc_hz: 997.84    rise_10_90_s: 0.000350    settle_time_s: 0.000735 (to 1 %)
```

The LED is a KT-0603R red LED. Its LCSC listing gives Vf = 1.8–2.4 V at 20 mA; 2.0 V is assumed at 2 mA.

```
$ tracectl tool calc.led_resistor vsupply=3.3 vf=2.0 current=2m
summary: "680 Ω (E24) gives 1.91 mA, resistor dissipates 2.49 mW"
```

The clamp's upper diode returns the input to 3V3, so a fault on J1 (for example 24 V) only pushes about 0.15 mA through
R3 into the rail. Full scale (12 V at J1) puts 3.0 V on the ADC pin, 0.3 V below the rail. Section 3 shows what that
margin costs.

## 2. Check the design

```
$ tracectl tool kicad.erc
errors: 0   warnings: 0   excluded: 0

$ tracectl tool kicad.drc            # with --schematic-parity
errors: 0   warnings: 0   unconnected: 0   parity_issues: 0

$ tracectl tool kicad.netlist
nets_total: 7   components_total: 10   single_pin_nets: 0
  /ADC_IN: C1.1 D1.3 J2.3 R3.2      /DIV: R1.2 R2.1 R3.1      GND: 7 pins ...

$ tracectl tool kicad.bom jlc=true
total_parts: 10   unique_lines: 10   missing_part_number: 0   lines_without_lcsc: 0

$ tracectl tool kicad.board trace_width_mm=0.25
outline 40 × 25 mm, 2 copper layers, 10 footprints, 7 nets, 23 tracks, 7 vias, 1 copper zone
F.Cu z0_ohm: 128.04 at 0.25 mm (microstrip over the 1.51 mm core)

$ tracectl tool kicad.net_length nets='["/ADC_IN"]' from=R3.2 to=J2.3
length_mm: 26.175 (the whole net)   path R3.2 → J2.3: 20.175 mm, 0 vias, 117 ps
```

ERC is clean because the design is complete, not because anything was waived. PWR_FLAGs mark 3V3 and GND as supplied
through J2 and J1, and every pin is connected, so no pin needs a no-connect flag. All 10 parts have an MPN and an LCSC
code, checked with `tracectl tool parts.lookup`, so the BOM has one line per part.

For a fab and assembly package, run `tracectl tool kicad.fab out_dir=build/fab`. It writes 17 files: Gerbers and drill zipped, the BOM, the JLCPCB BOM and CPL, and the placement file. All 10 parts get a placement, and there are no warnings.

## 3. Simulate it

The hand-written netlist, at the 12 V full-scale point:

```
$ tracectl tool sim.spice path=sim/front-end.cir --args '{"measurements":[
    {"name":"vadc_dc","kind":"value_at","vector":"v(adc_in)","analysis":"op"},
    {"name":"f3db","kind":"bandwidth","vector":"v(adc_in)"},
    {"name":"rise","kind":"rise_time","vector":"v(adc_in)","analysis":"tran"}]}'
vadc_dc: 2.99462 V     (calc.divider: 3.000 V, −0.18 %)
f3db:    1046 Hz       (calc.rc_filter: 998 Hz)
rise:    0.349 ms      (calc.rc_filter: 0.350 ms)
```

Mid-scale is the input range's middle, with no diode near conduction. Set `vin_dc` to 6:

```
$ tracectl tool sim.spice path=sim/front-end.cir --args '{"params":{"vin_dc":6},"analyses":[".op",".ac dec 50 1 1meg"], ...}'
vadc: 1.50002 V        f3db: 993.6 Hz   (calc.rc_filter 997.8 Hz: −0.4 %)
```

At mid-scale the filter matches the calculator. At the ends of the range the clamp loads the node: with `vin_dc=1`
the simulation gives 0.2588 V where the ideal is 0.25 V, and fc rises to 1095 Hz. The cause is the vendor model. Its
saturation current is IS = 34.9 µA, so it predicts tens of µA of reverse current. The BAT54S datasheet (Diodes Inc.
DS11005) gives at most 2.0 µA at 25 V reverse. The model is right about forward conduction, which is what the clamp
does, but it overstates leakage. An error budget should use the datasheet's 2 µA, which is about 32 mV through
15.95 kΩ in the worst case.

The schematic can be simulated directly, without the hand-written netlist (`sim/front-end-from-kicad.sh`):

```
$ tracectl tool sim.kicad_spice schematic=hardware/sensor-node.kicad_sch --args '{"analyses":[".op",".ac dec 50 1 1meg"],
    "replace":{"J1":"V1 /VIN 0 DC 6 AC 1","J2":"V2 +3V3 0 DC 3.3","D1":"XD1 GND +3V3 /ADC_IN BAT54S","D2":null,"R4":null}, ...}'
vadc: 1.50002 V        f3db: 993.566 Hz
netlist: components 10, replaced J1 D1 J2, removed R4 D2
```

This is the same answer as the hand-written netlist, so `front-end.cir` holds the schematic's values. KiCad's export
models the R and C parts itself. The connectors have no model, and neither do the Diode:BAT54S and Device:LED
symbols, so those are replaced or removed:

- D1 is replaced with the BAT54S subcircuit from `sim/models`.
- J1 and J2 are replaced with sources.
- The LED and R4 are removed.

## 4. The MCU side

```
$ tracectl tool sim.logic --args '{"files":["logic/moving_average.v","logic/moving_average_tb.v"],"top":"moving_average_tb","pass":"ALL TESTS PASSED"}'
passed: true
output: checked 254 samples / ALL TESTS PASSED
vcd: moving_average_tb.vcd (stored with the run, for sim.wave_read)

$ tracectl tool firmware.build target=adc-convert
ok: true   command: "make all test"   errors: 0   warnings: 0
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
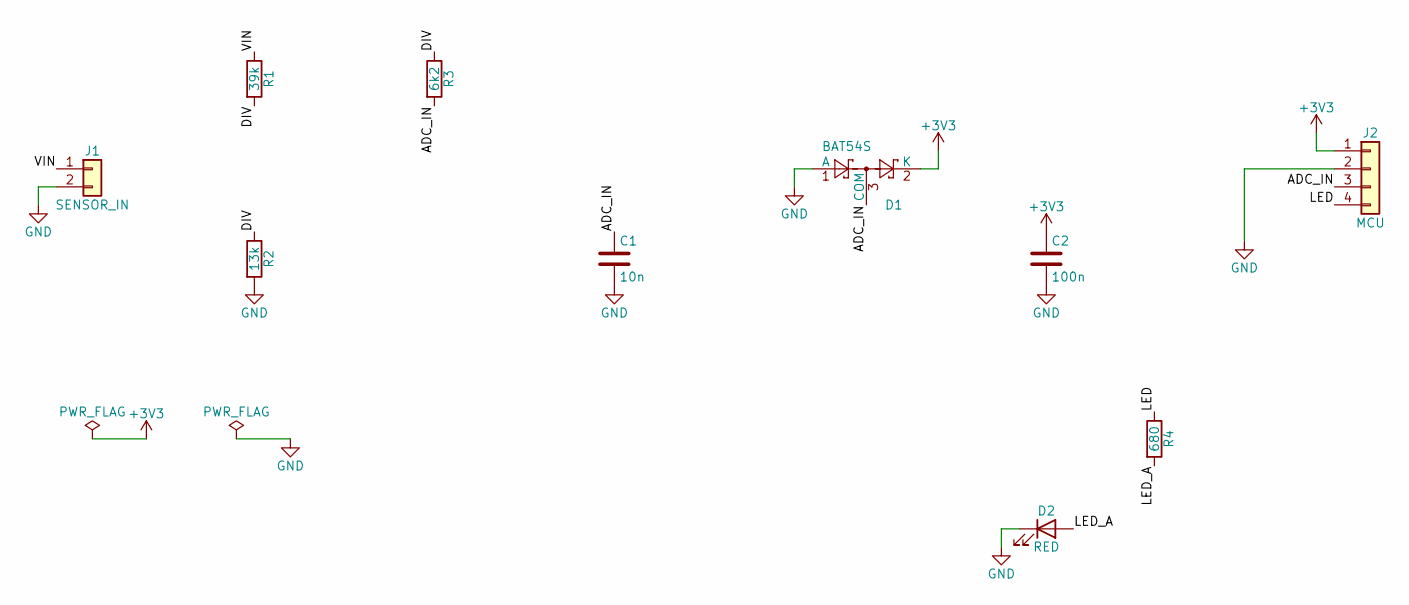
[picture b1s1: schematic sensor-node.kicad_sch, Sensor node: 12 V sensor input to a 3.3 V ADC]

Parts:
C1: 10n; C_0603_1608Metric; MPN CL10B103KB8NNNC; LCSC C1589
C2: 100n; C_0603_1608Metric; MPN CC0603KRX7R9BB104; LCSC C14663
D1: BAT54S; SOT-23; MPN BAT54S-7-F; LCSC C83574
D2: RED; LED_0603_1608Metric; MPN KT-0603R; LCSC C2286
J1: SENSOR_IN; PinHeader_1x02_P2.54mm_Vertical; MPN PZ254V-11-02P; LCSC C492401
J2: MCU; PinHeader_1x04_P2.54mm_Vertical; MPN PZ254V-11-04P; LCSC C2691448
R1: 39k; R_0603_1608Metric; MPN 0603WAF3902T5E; LCSC C23153
R2: 13k; R_0603_1608Metric; MPN 0603WAF1302T5E; LCSC C22797
R3: 6k2; R_0603_1608Metric; MPN 0603WAF6201T5E; LCSC C4260
R4: 680; R_0603_1608Metric; MPN 0603WAF6800T5E; LCSC C23228

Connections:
+3V3: C2.1, D1.2 (K), J2.1
/ADC_IN: C1.1, D1.3 (COM), J2.3, R3.2
/DIV: R1.2, R2.1, R3.1
/LED: J2.4, R4.1
/LED_A: D2.2 (A), R4.2
/VIN: J1.1, R1.1
GND: C1.2, C2.2, D1.1 (A), D2.1 (K), J1.2, J2.2, R2.2

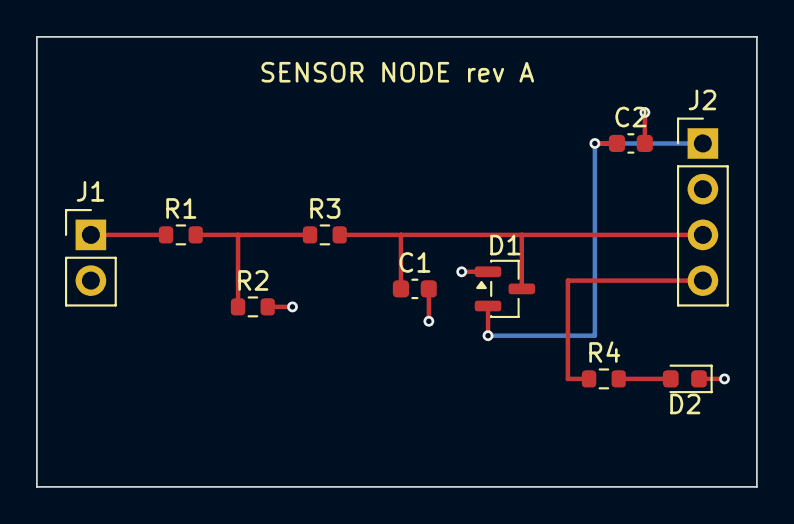
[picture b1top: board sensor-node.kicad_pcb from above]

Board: 2 copper layers, 40.0 x 25.0 mm, 10 parts (0 on the bottom side), 7 nets.

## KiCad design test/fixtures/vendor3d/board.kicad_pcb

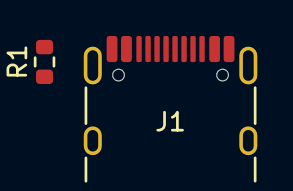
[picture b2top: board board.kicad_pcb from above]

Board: 0 copper layers, 3 parts (0 on the bottom side), 5 nets, no tracks yet.

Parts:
H3: MountingHole_2.2mm_M2
J1: TYPE-C-31-M-12; USB_C_Receptacle_HRO_TYPE-C-31-M-12
R1: 5.1k; R_0603_1608Metric

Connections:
/USB_DN: J1.A7, J1.B7
/USB_DP: J1.A6, J1.B6
/usb/CC1: J1.A5, R1.1
GND: J1.A1, J1.A12, J1.B1, J1.B12, J1.SH, R1.2
VBUS: J1.A4, J1.A9, J1.B4, J1.B9

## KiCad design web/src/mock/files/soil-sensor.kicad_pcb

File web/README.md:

# trace web app

The single-page app designed in [docs/ui-design.md](../docs/ui-design.md), wired as [docs/web-build.md](../docs/web-build.md) says.
React 19, Vite, TypeScript (strict), Tailwind CSS v4, shadcn/ui (new-york, neutral), TanStack Router (file routes), TanStack
Query, TanStack Table, CopilotKit v2 over AG-UI.

## Run it

```sh
cd web
npm install
VITE_API_ORIGIN=https://<your trace CloudFront address> npm run dev   # /api is proxied there
npm run dev:mock                                                    # no backend: fixtures (src/mock/), signed in as an admin
npm test                                                            # vitest + Testing Library (jsdom)
npm run build                                                       # tsc -b && vite build → web/dist
npm run screenshots                                                 # with dev:mock running: Playwright shots into screenshots/
node scripts/shots-systems.mjs                                      # the same for Admin › Connected systems (light, dark, phone)
```

From the repository root: `npm run build:web`, `npm run test:web`.

**Mock mode** (`VITE_MOCK=1`, development only) replaces `fetch` for `/api/*` with `src/mock/handlers.ts`, answering every action
the built screens call from `src/mock/fixtures.ts`, including sign-in (any email; the passkey and email-code choices sign in, the
password asks for a TOTP code — any six digits) and a streamed AG-UI reply at `/api/agui`. `main.tsx` only imports it behind
`import.meta.env.DEV`, so it is never in a production build. Add a case to `action()` when a new screen calls a new action.

## Layout

```
src/
  main.tsx              QueryClient, router, mock mode
  index.css             theme tokens (shadcn neutral + --primary, --verified, --warning, --waived), dark, density, motion, contrast
  routes/               file routes (routeTree.gen.ts is generated by the router plugin; commit it)
    __root.tsx          tooltips, toasts, display preferences
    _app.tsx            the signed-in shell: guard, live connection, CopilotKit, AppShell
    _app/…              screens with the rail: index (Home), inbox, projects/, p/$id (+ tabs under p/$id/)
    _focus.tsx          Focus mode: guard, live, CopilotKit, no shell
    _focus/p/$id/…      do/$skill, gates/$gate
    sign-in/, invite.$token.tsx, no-access.tsx
  lib/                  api.ts (call()), http.ts (body hash), auth.ts, live.ts, queries.ts, prefs.ts, theme.ts, format.ts,
                        glossary.ts, guard.ts, webauthn.ts, types.ts (every shape the app reads)
  components/
    ui/                 shadcn source (owned; edit freely)
    shell/              AppShell, Column, Section, sidebar, breadcrumbs (useCrumb), ⌘K (useCommands), bell, shortcuts
    chat/               provider, Ask trace panel, ChatView, EmbeddedChat, markdown, cards, renderers, recall, voice/
    data-table/         DataTable, Highlight, useUrlView
    focus/              FocusLayout
    canvas/             CanvasFrame
    stage-rail, next-step-card, needs-you-card, decision-card, evidence-chip, run-line, wait-line, quality-bar,
    status-badge, term (Term, Explained), rich (summaries with **bold**), states (Loading, EmptyState, ErrorState,
    QueryError, Partial, OfflineBanner, NotShared)
  mock/                 fixtures and the fetch handler
```

## Adding a screen

1. **Route file.** Create `src/routes/_app/<path>.tsx` (with the shell) or `src/routes/_focus/<path>.tsx` (Focus mode). The
   router plugin regenerates `routeTree.gen.ts` when `npm run dev` or `npm run build` runs. A placeholder may already exist
   (`NotBuilt`, or the project catch-all `routes/_app/p/$id/$.tsx`): replace it. For a project tab, add
   `routes/_app/p/$id/<tab>.tsx` — it wins over the catch-all — and its tab already shows in `visibleTabs()` (`p/$id.tsx`).

   ```tsx
   export const Route = createFileRoute('/_app/p/$id/evidence')({
     staticData: { crumb: 'Evidence' },          // the breadcrumb; useCrumb(routeId, label) to set one at run time
     validateSearch: z.record(z.string(), z.unknown()), // only when a Data table keeps its view in the address
     component: Evidence,
   })
   ```

2. **Data.** Read with `useAction('<action>', args)` or `useQuery(q('<action>', args))` (`lib/queries.ts`); every action and its
   types are in `lib/api.ts` → `Actions` (add a new one there first). Write with `useCall('<action>', (args) => [keys to
   invalidate])`. Never poll: the live connection invalidates by `[action, repo]` prefixes (`lib/live.ts`
   `invalidationsFor`), so key new reads the same way (`q()` does) and add the event mapping when a new kind of record changes.

3. **States.** Every screen draws all five: `Loading` (skeletons after 150 ms; show cached data at once), `EmptyState` (one sentence
   and the action that fills it), `Partial`, `QueryError` / `ErrorState` (what happened, whether anything was lost, Try again,
   detail folded), and the shell's `OfflineBanner`. A project the person cannot see is `NotShared` (same words whether it exists).

4. **Context for trace.** `useTraceContext({ label, description, value }, key)` tells the agent what is on screen and shows a
   removable chip in Ask trace. Use the key `'project'` with `value: { repo, … }` for the project in view (the panel picks its
   threads from it), `'screen'` for the screen, and your own for a selected item.

5. **Layout.** `<Column>` (the 960 px reading column) or `<Column wide>`; `<Section label="…" count={n} action={…}>` for the
   "NEEDS YOU" style headings. Phones: test at 390 px; tables turn into cards on their own.

6. **Mock.** Add fixture data and a case in `src/mock/handlers.ts`, so the screen renders under `npm run dev:mock`.

7. **Tests** sit beside the code (`*.test.ts(x)`), run in jsdom; see `components/data-table/data-table.test.tsx` for the pattern
   with a QueryClient.

Reference screens: Home (`routes/_app/index.tsx`), Projects (`routes/_app/projects/index.tsx`: a DataTable with columns,
URL view and row click), Project overview (`routes/_app/p/$id.tsx` + `p/$id/index.tsx`), and a Focus-mode frame
(`routes/_focus/p/$id/do/$skill.tsx`).

## Conventions

- **Words.** Plain and contextual (“Sign the schematic gate”, not “Approve”). Summaries from the API use `**bold**` for the
  recommendation; render them with `<Rich>`. Wrap technical words in `<Term>` or text in `<Explained>`.
- **Colour.** The accent (`primary`) only for the person's move. Status always as `<StatusBadge>` (icon + word).
- **Requests.** Always through `call()` / `api()` (`lib/api.ts`): they add the bearer token and the `x-amz-content-sha256` body
  hash CloudFront's origin access control needs on POST/PUT, and refresh once on 401. Tokens live in memory only.
- **Heavy code is lazy.** Markdown/KaTeX, Shiki (per language), Mermaid, Recharts and QR load on first use; keep new viewers
  (KiCanvas, PDF.js, three.js, Cytoscape) behind `lazy()`/`import()` too. Register file viewers with `registerFileViewer()`.
- **Chat.** CopilotKit v2 with trace's agent as a self-managed AG-UI `HttpAgent` at `/api/agui` (no CopilotKit runtime; the web
  backend checks access on every request). Tool calls draw by result shape (`chat/renderers.tsx`); `ask_person` is the
  human-in-the-loop Decision card.

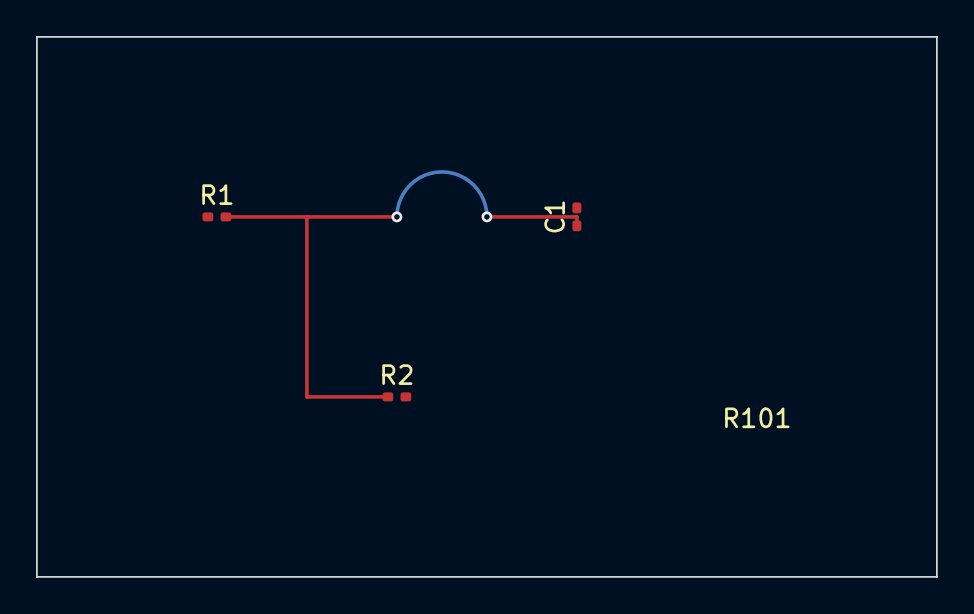
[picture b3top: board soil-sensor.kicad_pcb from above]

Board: 4 copper layers, 50.0 x 30.0 mm, 4 parts (1 on the bottom side), 2 nets.

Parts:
C1: 100n; C_0402_1005Metric
R1, R2: 10k; R_0402_1005Metric
R101: 4k7; R_0402_1005Metric

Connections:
GND: C1.2, R2.2
MID: C1.1, R1.2, R2.1, R101.1

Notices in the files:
README.md:
through `bedrock-agent-runtime`; each hit has its text, score, path, commit and a citation: `path@commit`, or the part,
examples/sensor-node/README.md:
`datasheets.add` and cite their pages to firm these up.
